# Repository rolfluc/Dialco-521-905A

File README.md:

Repo housing the Schematic and PCB design for a replicate Dialco-521-905A

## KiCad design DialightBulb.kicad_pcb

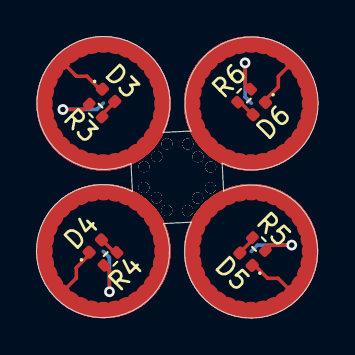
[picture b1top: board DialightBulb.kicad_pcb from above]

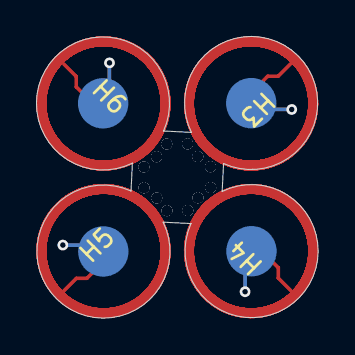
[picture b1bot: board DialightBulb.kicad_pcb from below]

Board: 2 copper layers, 15.6 x 15.6 mm, 140 parts (4 on the bottom side), 3 nets.

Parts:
D3, D4, D5, D6: LED; LED_0402_1005Metric
H3, H4, H5, H6: MountingHole_Pad; CenterPower
N3, N4, N5, N6, N7, N8, N9, N10, N11, N12, N13, N14, N15, N16, N17, N18, N19, N20, N21, N22, N23, N24, N25, N26, N27, N28, N29, N30, N31, N32, N33, N34, N35, N36, N37, N38, N39, N40, N41, N42, N43, N44, N45, N46, N47, N48, N49, N50, N51, N52, N53, N54, N55, N56, N57, N58, N59, N60, N61, N62, N63, N64, N65, N66, N67, N68, N69, N70, N71, N72, N73, N74, N75, N76, N77, N78, N79, N80, N81, N82, N83, N84, N85, N86, N87, N88, N89, N90, N91, N92, N93, N94, N95, N96, N97, N98, N99, N100, N101, N102, N103, N104, N105, N106, N107, N108, N109, N110, N111, N112, N113, N114, N115, N116, N117, N118, N119, N120, N121, N122, N123, N124, N125, N126, N127, N128, N129, N130: Housing_Pad; GroundRing
R3, R4, R5, R6: R; R_0402_1005Metric

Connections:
/VLED: H3.1, H4.1, H5.1, H6.1, R3.2, R4.2, R5.2, R6.2
GND: D3.1 (K), D4.1 (K), D5.1 (K), D6.1 (K), N3.1 (PAD), N4.1 (PAD), N5.1 (PAD), N6.1 (PAD), N7.1 (PAD), N8.1 (PAD), N9.1 (PAD), N10.1 (PAD), N11.1 (PAD), N12.1 (PAD), N13.1 (PAD), N14.1 (PAD), N15.1 (PAD), N16.1 (PAD), N17.1 (PAD), N18.1 (PAD), N19.1 (PAD), N20.1 (PAD), N21.1 (PAD), N22.1 (PAD), N23.1 (PAD), N24.1 (PAD), N25.1 (PAD), N26.1 (PAD), N27.1 (PAD), N28.1 (PAD), N29.1 (PAD), N30.1 (PAD), N31.1 (PAD), N32.1 (PAD), N33.1 (PAD), N34.1 (PAD), N35.1 (PAD), N36.1 (PAD), N37.1 (PAD), N38.1 (PAD), N39.1 (PAD), N40.1 (PAD), N41.1 (PAD), N42.1 (PAD), N43.1 (PAD), N44.1 (PAD), N45.1 (PAD), N46.1 (PAD), N47.1 (PAD), N48.1 (PAD), N49.1 (PAD), N50.1 (PAD), N51.1 (PAD), N52.1 (PAD), N53.1 (PAD), N54.1 (PAD), N55.1 (PAD), N56.1 (PAD), N57.1 (PAD), N58.1 (PAD), N59.1 (PAD), N60.1 (PAD), N61.1 (PAD), N62.1 (PAD), N63.1 (PAD), N64.1 (PAD), N65.1 (PAD), N66.1 (PAD), N67.1 (PAD), N68.1 (PAD), N69.1 (PAD), N70.1 (PAD), N71.1 (PAD), N72.1 (PAD), N73.1 (PAD), N74.1 (PAD), N75.1 (PAD), N76.1 (PAD), N77.1 (PAD), N78.1 (PAD), N79.1 (PAD), N80.1 (PAD), N81.1 (PAD), N82.1 (PAD), N83.1 (PAD), N84.1 (PAD), N85.1 (PAD), N86.1 (PAD), N87.1 (PAD), N88.1 (PAD), N89.1 (PAD), N90.1 (PAD), N91.1 (PAD), N92.1 (PAD), N93.1 (PAD), N94.1 (PAD), N95.1 (PAD), N96.1 (PAD), N97.1 (PAD), N98.1 (PAD), N99.1 (PAD), N100.1 (PAD), N101.1 (PAD), N102.1 (PAD), N103.1 (PAD), N104.1 (PAD), N105.1 (PAD), N106.1 (PAD), N107.1 (PAD), N108.1 (PAD), N109.1 (PAD), N110.1 (PAD), N111.1 (PAD), N112.1 (PAD), N113.1 (PAD), N114.1 (PAD), N115.1 (PAD), N116.1 (PAD), N117.1 (PAD), N118.1 (PAD), N119.1 (PAD), N120.1 (PAD), N121.1 (PAD), N122.1 (PAD), N123.1 (PAD), N124.1 (PAD), N125.1 (PAD), N126.1 (PAD), N127.1 (PAD), N128.1 (PAD), N129.1 (PAD), N130.1 (PAD)
unnamed: D3.2 (A), D4.2 (A), D5.2 (A), D6.2 (A), R3.1, R4.1, R5.1, R6.1
